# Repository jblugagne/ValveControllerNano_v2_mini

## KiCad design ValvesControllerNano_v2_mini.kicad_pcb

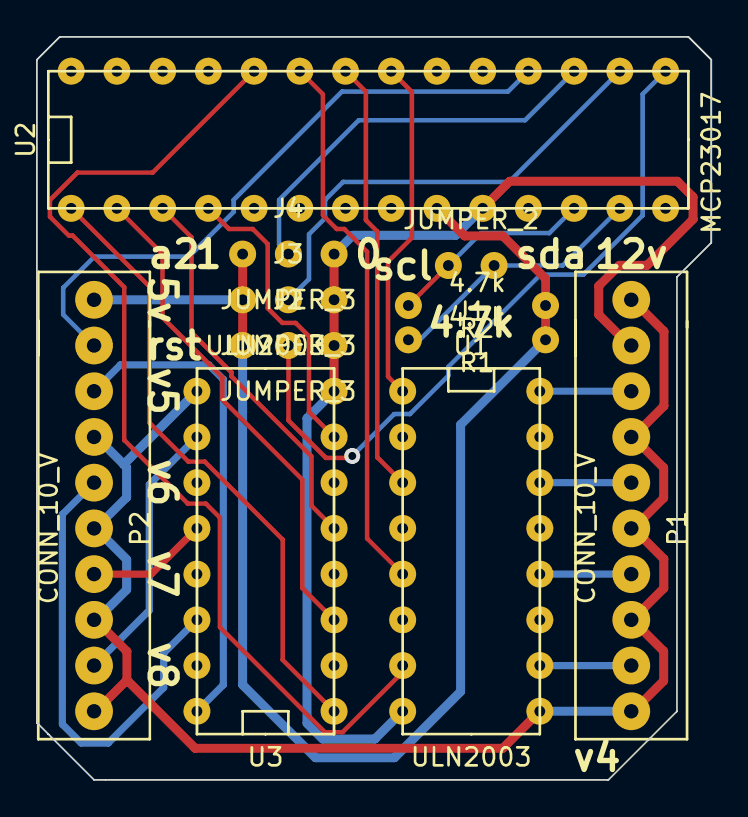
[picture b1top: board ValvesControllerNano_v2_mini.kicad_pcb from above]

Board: 2 copper layers, 37.5 x 41.3 mm, 11 parts (0 on the bottom side), 25 nets.

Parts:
J1: JUMPER_2; jumper_2
J2, J3, J4: JUMPER_3; jumper_3
P1, P2: CONN_10_V; bornier10
R1, R2: 4.7k; resistor
U1, U3: ULN2003; uln2003
U2: MCP23017; mcp23017_pdip

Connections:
+5V: J2.1, J3.1, J4.1, P2.1, R1.1, R2.1, U2.9
+12V: P1.1, P1.4, P1.6, P1.8, P1.10, P2.4, P2.6, P2.8, P2.10, U1.9, U3.9
/RST: P2.2, U2.18
/v01_05: U1.1, U2.21
/v01_12: P1.3, U1.16
/v02_05: U1.3, U2.22
/v03_05: U1.5, U2.23
/v03_12: P1.7, U1.12
/v04_05: U1.7, U2.24
/v04_12: P1.9, U1.10
/v05_05: U2.1, U3.1
/v05_12: P2.3, U3.16
/v06_05: U2.2, U3.3
/v06_12: P2.5, U3.14
/v07_05: U2.3, U3.5
/v07_12: P2.7, U3.12
/v08_05: U2.4, U3.7
/v08_12: P2.9, U3.10
/v_02_12: P1.5, U1.14
A0: J2.2, U2.15
A1: J3.2, U2.16
A2: J4.2, U2.17
GND: J2.3, J3.3, J4.3, P1.2, U1.8, U2.10, U3.8
SCL: J1.2, R2.2, U2.12
SDA: J1.1, R1.2, U2.13

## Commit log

2016-02-22 Q&D version for OSH
2016-02-25 added a 3-way switch for adress setting...
